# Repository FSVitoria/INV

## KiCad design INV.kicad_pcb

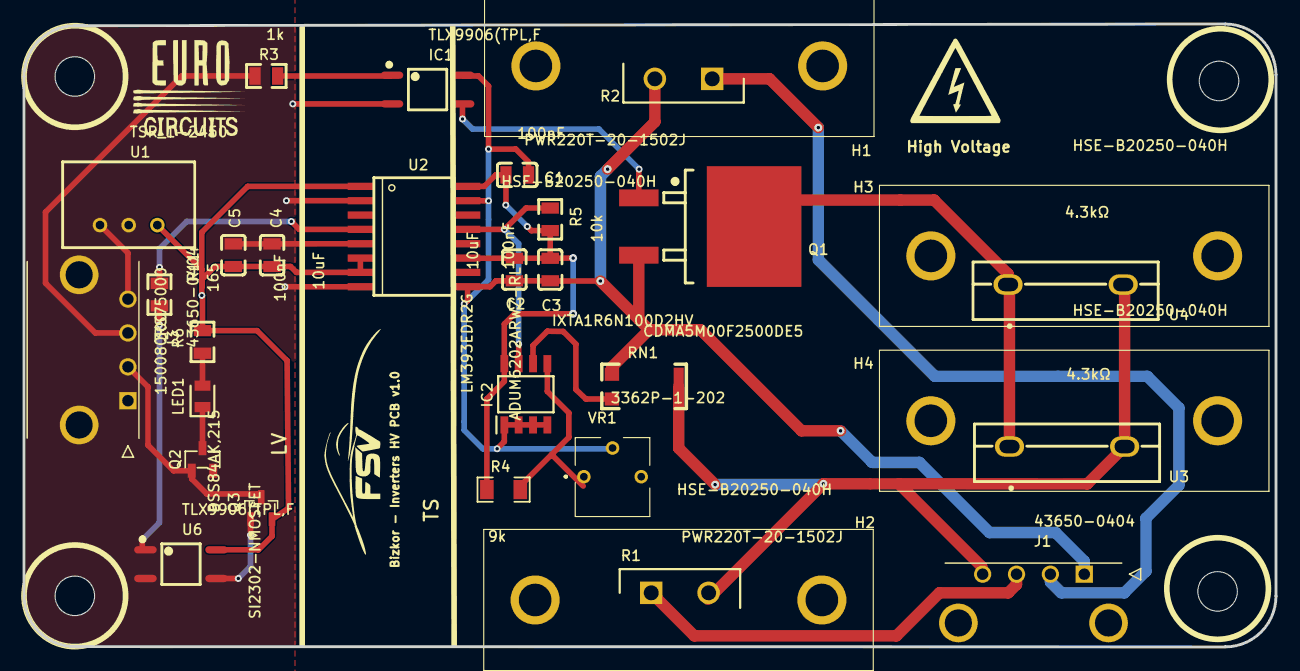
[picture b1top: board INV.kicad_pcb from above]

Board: 2 copper layers, 110.9 x 55.2 mm, 35 parts (0 on the bottom side), 21 nets.

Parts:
C1, C3, C5: 100nF; C0805
C2, C4: 10uF; C0805
H1, H2, H3, H4: HSE-B20250-040H; HSEB20250040H
Hole_gge3595: Hole_gge3595
Hole_gge3710: Hole_gge3710
Hole_gge3725: Hole_gge3725
Hole_gge3740: Hole_gge3740
IC1: TLX9906(TPL,F; SOIC-4_L3.6-W4.4-P2.54-LS7.0-TL
IC2: LM393EDR2G; SOIC127P600X175-8N
J1, J3: 43650-0404; 43650-04YY_03040559
LED1: 150080RS75000; LEDC2012X80N
Q1: IXTA1R6N100D2HV; TO-263-3_L10.2-W10.7-P5.08-LS16.2-BR
Q2: SI2302-NMOSFET; SOT-23-3_L2.9-W1.3-P1.90-LS2.4-BR
Q3: BSS84AK,215; SOT95P230X110-3N
R1, R2: PWR220T-20-1502J; TO508P344X1041X2058-2P
R3: 1k; R0805
R4: 9k; R1206
R5: 10k; R0805
R6: 300; R0805
R11: 165; R0805
RN1: CDMA5M00F2500DE5; CDMA15M0D2500DE5
U1: TSR_1-2450; TSR-1-24120
U2: ADUM6202ARWZ-RL; SOIC16E
U3, U4: 4.3kΩ; TO-247-2_L15.8-W5.0-P10.20-L
U6: TLX9906(TPL,F; SOIC-4_L3.6-W4.4-P2.54-LS7.0-TL
VR1: 3362P-1-202; 3362P1103RLF

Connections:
+5V: C4.2, C5.2, Q3.2, R6.2, U1.3, U2.1, U2.6, U2.7, U6.6
+5VISO: C1.1, C2.2, C3.2, IC2.8, R4.2, R5.2, U2.11, U2.16
+24V: J3.4, U1.1
GND: C4.1, C5.1, IC1.3, J3.1, Q2.2, U1.2, U2.2, U2.5, U2.8, U6.3
IC2_6: IC2.6, RN1.3
LED1_1: LED1.1, Q2.3
LED1_2: LED1.2, R6.1
Q1_1: IC1.4, Q1.1
Q1_2: Q1.2, U3.1, U4.1
R3_2: IC1.1, R3.2
R5_1: IC2.7, R5.1, U2.13
SDC_IN: J3.3, R3.1
TS+: J1.4, R1.2, RN1.1, U3.2, U4.2
TS-: C1.2, C2.1, C3.1, IC1.6, IC2.1, IC2.2, IC2.3, IC2.4, J1.1, Q1.3, R2.2, RN1.2, U2.9, U2.15, VR1.2
TSMP+: J1.3, R1.1
TSMP-: J1.2, R2.1
TS_ACTIVE_INV: R11.1, U2.4
TS_ACTIVE_INV_OUT: J3.2, Q2.1, Q3.3
U6_1: R11.2, U6.1
U6_4: Q3.1, U6.4
VR1_1: IC2.5, R4.1, VR1.1
